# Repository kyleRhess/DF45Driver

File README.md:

# DF45 Motor Driver

## A low-level Arduino sketch for controlling the [Nanotec DF45](https://us.nanotec.com/products/1544-df45-brushless-dc-motor/) BLDC (Brushless DC) motor

\
\
This code was written for the Arduino Uno or any ATMega328.
\
The [motor driver module itself](https://kylerhess.github.io/driver.html) uses an embedded `ATMEGA328-AUR` and is proprietary to the controller PCB design.
\
The DF45 Driver relies on brushless motors with Hall-Effect sensor feedback in order to function properly. These motors operate under `Four Quadrant Motor Control`.

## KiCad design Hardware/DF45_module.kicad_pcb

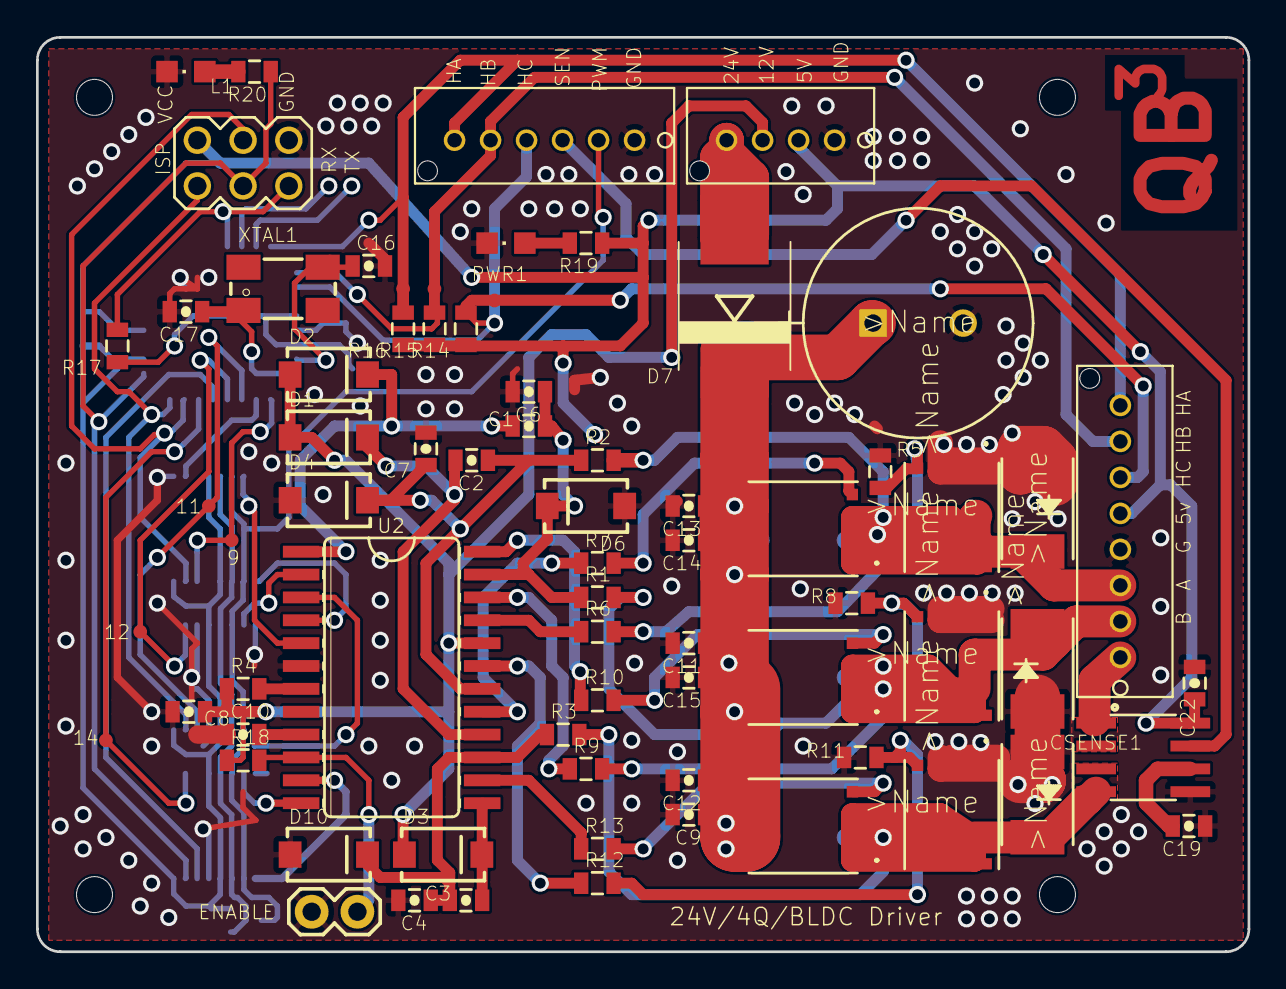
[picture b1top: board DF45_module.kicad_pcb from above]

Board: 2 copper layers, 67.3 x 50.8 mm, 89 parts (0 on the bottom side), 56 nets.

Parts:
@HOLE0, @HOLE1, @HOLE2, @HOLE3: (no value)
C1, C2, C3: 0.22uF; 0805-CAP
C4, C6, C7, C19, C22: 1nF; 0805-CAP
C8, C11, C12, C13: 1uF; 0805-CAP
C9, C14, C15: 20nF; 0805-CAP
C10: 470pF; 0805-CAP
C16, C17: 22pF; 0805-CAP
C18, C20, C21: 0.1uF; 0805-CAP
C23: 1000uF; PCAP_125X25
CR1, CR2, CR3, CR4, CR5, CR6: SD2114S040S8R0; SD2114
CSENSE1: ACS712; SO08
D1, D2, D3, D4, D6, D10: DIODESMA; SMA-DIODE
D7: SCHOTTKY-DIODESMC; SMC
J1: M02PTH; 1X02
L1: LEDCHIPLED_0805; CHIPLED_0805
PWR1: LEDCHIPLED_0805; CHIPLED_0805
Q1, Q2, Q3, Q4, Q5, Q6: CSD18537NQ5A; DQJ8
R1, R2, R3, R6, R7, R9, R10, R12, R13: 4.7; 0805
R4: 15k; 0805
R5, R8, R11: 20k; 0805
R14, R15, R16, R17, R18, R20: 10k; 0805
R19: 300; 0805
SV1: MA03-2
TP1, TP2, TP3, TP4, TP5, TP6, TP7, TP8, TP9: TEST-POINT3; PAD.03X.03
U2: HIP408624-SOIC; 24-SOIC
U3, U4, U5: 74HC153TSSOP-16; TSSOP-16
U6: 741G04DCK; SC70-5
U7: ATMEGA328-AUR; 32A
U$1: PA-CON8TH; PA-CON
U$2: PA-CON6
U$4: PA-CON4
XTAL1: CRYSTALCTS406; CTS406

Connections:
/5V: C18.1, C20.1, C21.2, C22.1, CSENSE1.8, R14.1, R15.1, R16.1, R17.1, R19.1, SV1.2, U3.4, U3.12, U3.16, U4.4, U4.12, U4.16, U5.4, U5.12, U5.16, U6.5, U7.4, U7.6, U7.18, U7.20, U$1.6, U$4.2
/12V: C8.1, D1.A, D2.A, D3.A, R4.1, R18.1, U2.20, U$4.3
/24V: D7.A, U$4.4
/AE: SV1.4, U3.15, U7.15
/AHI: U2.5, U3.7
/AHO: R7.1, U2.17
/ALI: U2.4, U3.9
/ALO: R6.1, U2.21
/AS1: TP1.P$1, U3.14, U7.9
/AS2: TP5.P$1, U3.2, U7.10
/BE: SV1.1, U4.15, U7.16
/BHI: U2.2, U4.7
/BHO: R10.1, U2.24
/BLI: U2.3, U4.9
/BLO: R9.1, U2.22
/BS1: TP7.P$1, U4.14, U7.11
/BS2: TP6.P$1, U4.2, U7.12
/CE: R20.1, SV1.3, U5.15, U7.17
/CHI: U2.12, U5.7
/CHO: R13.1, U2.14
/CLI: U2.11, U5.9
/CLO: R12.1, U2.19
/CS1: TP9.P$1, U5.14, U7.13
/CS2: TP8.P$1, U5.2, U7.14
/DIS: J1.1, R18.2, U2.10
/FILT: C19.2, CSENSE1.6
/HAL_A: R16.2, TP2.P$1, U7.32, U$1.9, U$2.6
/HAL_B: R15.2, TP3.P$1, U7.1, U$1.8, U$2.5
/HAL_C: R14.2, TP4.P$1, U7.2, U$1.7, U$2.4
/MOS: C9.1, C11.1, C12.1, C13.1, C14.1, C15.1, C23.1, CR1.1, CR3.1, CR5.1, D7.C, Q1.5, Q1.6, Q1.7, Q1.8, Q3.5, Q3.6, Q3.7, Q3.8, Q5.5, Q5.6, Q5.7, Q5.8
/PHA: CR1.2, CR2.1, Q1.1, Q1.2, Q1.3, Q2.5, Q2.6, Q2.7, Q2.8, R2.2, U$1.4
/PHB: CR3.2, CR4.1, Q3.1, Q3.2, Q3.3, Q4.5, Q4.6, Q4.7, Q4.8, R1.2, U$1.3
/PHC: CR5.2, CR6.1, CSENSE1.1, CSENSE1.2, CSENSE1.3, CSENSE1.4, Q5.1, Q5.2, Q5.3, Q6.5, Q6.6, Q6.7, Q6.8, R3.2, U$1.2
/PWM: U3.6, U3.10, U4.6, U4.10, U5.6, U5.10, U6.2, U$2.2
/RST: R17.2, SV1.5, U7.29
/SENSE: CSENSE1.7, U$2.3
/~PWM~: U3.5, U3.11, U4.5, U4.11, U5.5, U5.11, U6.4
GND: C4.2, C6.2, C7.2, C8.2, C9.2, C10.1, C11.2, C12.2, C13.2, C14.2, C15.2, C16.2, C17.2, C18.2, C19.1, C20.2, C21.1, C22.2, C23.2, CR2.2, CR4.2, CR6.2, CSENSE1.5, D4.A, D6.A, D10.A, J1.2, L1.C, PWR1.C, Q2.1, Q2.2, Q2.3, Q4.1, Q4.2, Q4.3, Q6.1, Q6.2, Q6.3, R5.1, R8.1, R11.1, SV1.6, U2.6, U3.1, U3.3, U3.8, U3.13, U4.1, U4.3, U4.8, U4.13, U5.1, U5.3, U5.8, U5.13, U6.3, U7.3, U7.5, U7.21, U$1.5, U$2.1, U$4.1
unnamed: C1.1, D2.C, U2.1
unnamed: C1.2, C6.1, D6.C, R1.1, U2.23
unnamed: C2.1, C7.1, D4.C, R2.1, U2.18
unnamed: C2.2, D1.C, U2.16
unnamed: C3.1, C4.1, D10.C, R3.1, U2.15
unnamed: C3.2, D3.C, U2.13
unnamed: C10.2, U2.9
unnamed: C16.1, U7.7, XTAL1.3
unnamed: C17.1, U7.8, XTAL1.1
unnamed: L1.A, R20.2
unnamed: PWR1.A, R19.2
unnamed: Q1.4, R7.2
unnamed: Q2.4, R5.2, R6.2
unnamed: Q3.4, R10.2
unnamed: Q4.4, R8.2, R9.2
unnamed: Q5.4, R13.2
unnamed: Q6.4, R11.2, R12.2
unnamed: R4.2, U2.7

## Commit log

2017-06-20 Rename DriverBoardRev@.ino to DriverBoardRev2.ino
2020-01-25 Added hardware files.
2020-01-27 Updated hardware to use latest library references.
